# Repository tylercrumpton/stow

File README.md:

# S.T.O.W Module
*Synapse Tactical Occluded Wireless module - mPCIe Synapse Wireless SM200 card*

S.T.O.W is laptop wireless card based on the Synapse SM200 SNAP module, a microcontroller with built-in 802.15.4 wireless meshing that runs Python scripts. It allows you to have a bridge node built into a laptop without having to carry a separate USB device around that sticks out from a USB port!

**NOTE**: This design has not been tested and is currently for illustrative purposes only. If you'd like to check out the design, you're good, but don't expect to send this off to a fab house and get a working board!

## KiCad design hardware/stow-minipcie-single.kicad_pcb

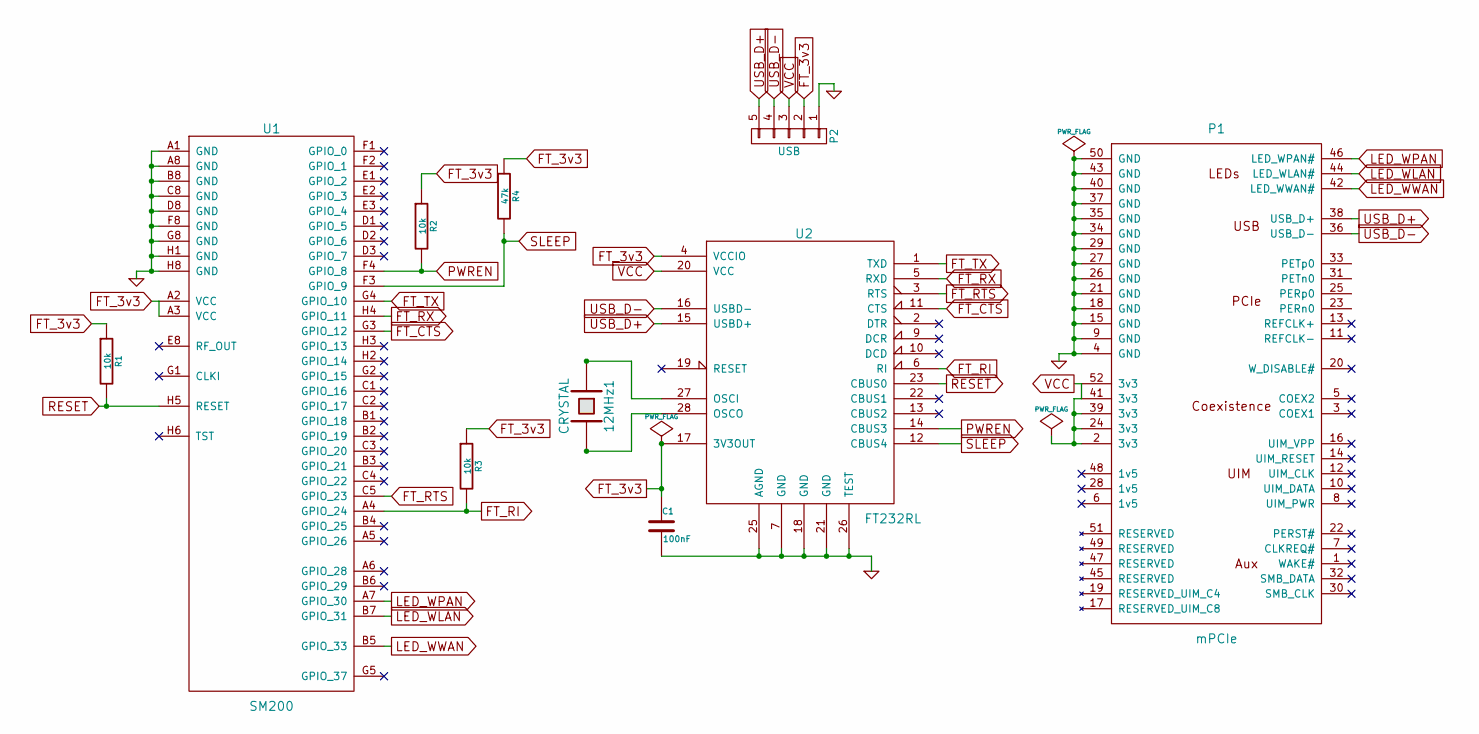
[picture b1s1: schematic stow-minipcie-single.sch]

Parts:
12MHz1: CRYSTAL; Crystal_HC49-SD_SMD
C1: 100nF; C_0805_HandSoldering
P1: mPCIe; MPCIe_full_card
P2: USB; Pin_Header_Straight_1x05
R1, R2, R3: 10k; R_0805_HandSoldering
R4: 47k; R_0805_HandSoldering
U1: SM200
U2: FT232RL; SSOP-28_5.3x10.2mm_Pitch0.65mm

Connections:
FT_3v3: C1.1, P2.2, R1.1, R2.1, R3.1, R4.1, U1.A2 (VCC), U1.A3 (VCC), U2.4 (VCCIO), U2.17 (3V3OUT)
FT_CTS: U1.G3 (GPIO_12), U2.11 (CTS)
FT_RI: R3.2, U1.A4 (GPIO_24), U2.6 (RI)
FT_RTS: U1.C5 (GPIO_23), U2.3 (RTS)
FT_RX: U1.H4 (GPIO_11), U2.5 (RXD)
FT_TX: U1.G4 (GPIO_10), U2.1 (TXD)
GND: C1.2, P1.4 (GND), P1.9 (GND), P1.15 (GND), P1.18 (GND), P1.21 (GND), P1.26 (GND), P1.27 (GND), P1.29 (GND), P1.34 (GND), P1.35 (GND), P1.37 (GND), P1.40 (GND), P1.43 (GND), P1.50 (GND), P2.1, U1.A1 (GND), U1.A8 (GND), U1.B8 (GND), U1.C8 (GND), U1.D8 (GND), U1.F8 (GND), U1.G8 (GND), U1.H1 (GND), U1.H8 (GND), U2.7 (GND), U2.18 (GND), U2.21 (GND), U2.25 (AGND), U2.26 (TEST)
LED_WLAN: P1.44 (LED_WLAN#), U1.B7 (GPIO_31)
LED_WPAN: P1.46 (LED_WPAN#), U1.A7 (GPIO_30)
LED_WWAN: P1.42 (LED_WWAN#), U1.B5 (GPIO_33)
unnamed 10: 12MHz1.1, U2.27 (OSCI); also elsewhere on the board
unnamed 11: 12MHz1.2, U2.28 (OSCO); also elsewhere on the board
PWREN: R2.2, U1.F4 (GPIO_8), U2.14 (CBUS3)
RESET: R1.2, U1.H5 (RESET), U2.23 (CBUS0)
SLEEP: R4.2, U1.F3 (GPIO_9), U2.12 (CBUS4)
USB_D+: P1.38 (USB_D+), P2.5, U2.15 (USBD+)
USB_D-: P1.36 (USB_D-), P2.4, U2.16 (USBD-)
VCC: P1.2 (3v3), P1.24 (3v3), P1.39 (3v3), P1.41 (3v3), P1.52 (3v3), P2.3, U2.20 (VCC)

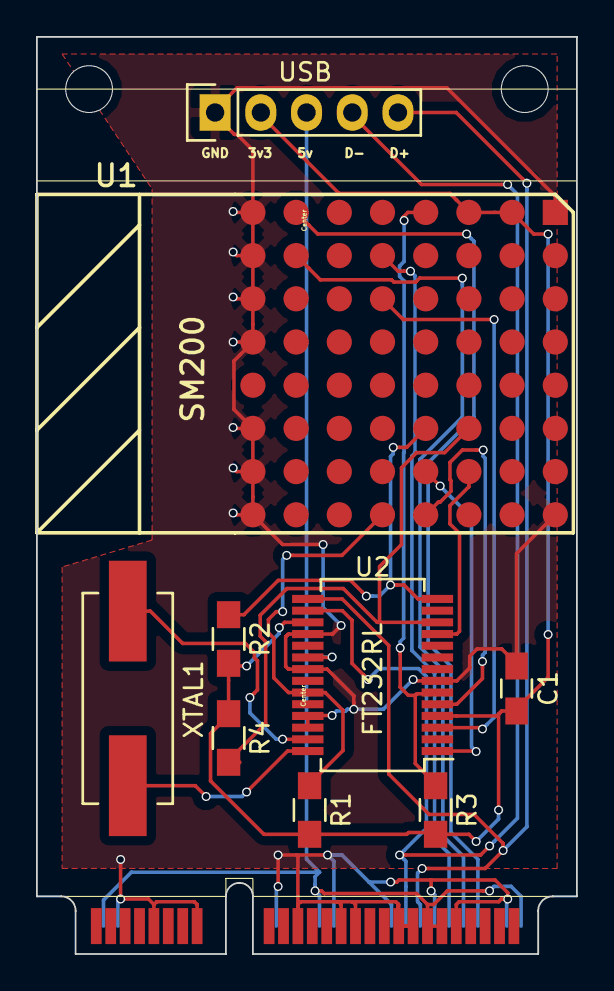
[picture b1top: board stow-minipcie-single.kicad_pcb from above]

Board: 2 copper layers, 30.0 x 51.0 mm, 10 parts (0 on the bottom side), 18 nets.

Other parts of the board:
XTAL1: CRYSTAL; Crystal_HC49-SD_SMD

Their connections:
unnamed 10: XTAL1.1; also elsewhere on the board
unnamed 11: XTAL1.2; also elsewhere on the board

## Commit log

2015-07-15 Initial project creation.
2015-08-05 Add start of schematic capture.
2015-08-05 Add FTDI chip to schematic.
2015-08-05 Add some schematic connections.
2015-09-17 Hooked up UART1 and RI.
2015-09-17 Wired up RESET pin.
2015-09-17 Wire up PWREN and SLEEP pin.
2015-09-17 Add external xtal for 3v3 operation.
2015-09-20 Wire up some power connections.
2015-09-20 Wire up status LED signals.
2015-09-20 Wire up remaining GNDs and power.
2015-09-20 Add no-connects for unused pins.
2015-09-20 Fix a few DRC errors.
2015-09-20 Add external USB debugging/programming port.
2015-09-21 Add submodules and update library links.
2015-09-21 Update CrumpPrints submodule reference.
2015-09-21 Add .cmp file for PCB.
2015-09-21 Create first shot at placement and outline.
2015-09-21 Route the whole board.
2015-10-14 Move and add silkscreen labels.
2015-10-14 Use fixed connector pad layer footprint.
2015-10-14 Add back silkscreen.
2015-10-14 Fix more silkscreen.
2015-10-14 Create README file.
2015-10-14 Add LICENSE file.
2015-10-14 Change version label to v1.0.
2017-03-24 Ad pictures and note to README.

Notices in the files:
hardware/stow-minipcie-single.kicad_pcb:
CC-BY-SA 4.0
